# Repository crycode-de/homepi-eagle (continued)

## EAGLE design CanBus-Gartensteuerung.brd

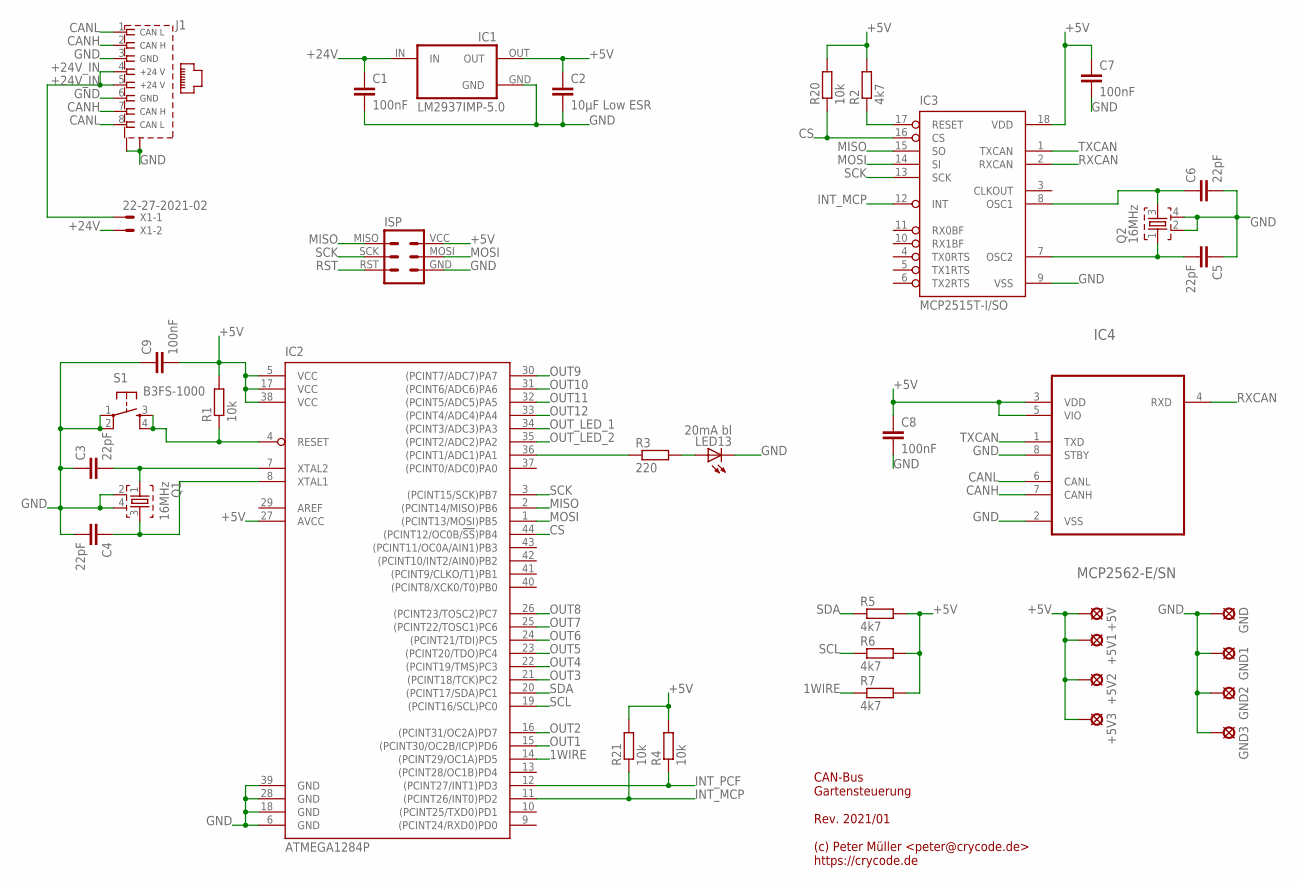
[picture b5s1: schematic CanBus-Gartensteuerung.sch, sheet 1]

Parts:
+5V, +5V1, +5V2, +5V3: LSP13
C1, C7, C8, C9: 100nF; C0805
C2: 10µF Low ESR; C0805
C3, C4, C5, C6: 22pF; C0805
GND, GND1, GND2, GND3: LSP13
IC1: LM2937IMP-5.0; SOT223
IC2: ATMEGA1284P; TQFP44
IC3: MCP2515T-I/SO; SO18L
IC4: MCP2562-E/SN; SO08
ISP: ISPVIAS-ONLY-1.27MM; ISP-VIAS-ONLY-1.27MM
J1: RJ45-CAN; MEBP_8-8G
LED13: 20mA bl; CHIPLED_0805
Q1, Q2: 16MHz; MJ-5X3.2
R1, R4, R20, R21: 10k; R0805
R2, R5, R6, R7: 4k7; R0805
R3: 220; R0805
S1: B3FS-1000
X1: 22-27-2021-02; 6410-02

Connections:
1WIRE: IC2.14 ((PCINT29/OC1A)PD5), R7.1; also elsewhere on the board
+5V: +5V.MP, +5V1.MP, +5V2.MP, +5V3.MP, C2.1, C7.1, C8.1, C9.2, IC1.OUT, IC2.5 (VCC), IC2.17 (VCC), IC2.27 (AVCC), IC2.38 (VCC), IC3.18 (VDD), IC4.3 (VDD), IC4.5 (VIO), ISP.VCC, R1.2, R2.2, R4.2, R5.2, R6.2, R7.2, R20.2, R21.2; also elsewhere on the board
+24V: C1.1, IC1.IN, X1.2; also elsewhere on the board
+24V_IN: J1.4, J1.5, X1.1
CANH: IC4.7 (CANH), J1.2, J1.7
CANL: IC4.6 (CANL), J1.1, J1.8
CS: IC2.44 ((PCINT12/OC0B/!SS!)PB4), IC3.16 (CS), R20.1
GND: C1.2, C2.2, C3.1, C4.2, C5.1, C6.2, C7.2, C8.2, C9.1, GND.MP, GND1.MP, GND2.MP, GND3.MP, IC1.GND, IC1.GND@ (GND), IC2.6 (GND), IC2.18 (GND), IC2.28 (GND), IC2.39 (GND), IC3.9 (VSS), IC4.2 (VSS), IC4.8 (STBY), ISP.GND, J1.3, J1.6, J1.G1 (S1), J1.G2 (S2), LED13.C, Q1.2, Q1.4, Q2.2, Q2.4, S1.1, S1.2 (P1); also elsewhere on the board
INT_MCP: IC2.11 ((PCINT26/INT0)PD2), IC3.12 (INT), R21.1
INT_PCF: IC2.12 ((PCINT27/INT1)PD3), R4.1; also elsewhere on the board
MISO: IC2.2 ((PCINT14/MISO)PB6), IC3.15 (SO), ISP.MISO
MOSI: IC2.1 ((PCINT13/MOSI)PB5), IC3.14 (SI), ISP.MOSI
unnamed: IC3.17 (RESET), R2.1
unnamed: IC2.36 ((PCINT1/ADC1)PA1), R3.1
unnamed: LED13.A, R3.2
OUT1: IC2.15 ((PCINT30/OC2B/ICP)PD6); also elsewhere on the board
OUT2: IC2.16 ((PCINT31/OC2A)PD7); also elsewhere on the board
OUT3: IC2.21 ((PCINT18/TCK)PC2); also elsewhere on the board
OUT4: IC2.22 ((PCINT19/TMS)PC3); also elsewhere on the board
OUT5: IC2.23 ((PCINT20/TDO)PC4); also elsewhere on the board
OUT6: IC2.24 ((PCINT21/TDI)PC5); also elsewhere on the board
OUT7: IC2.25 ((PCINT22/TOSC1)PC6); also elsewhere on the board
OUT8: IC2.26 ((PCINT23/TOSC2)PC7); also elsewhere on the board
OUT9: IC2.30 ((PCINT7/ADC7)PA7); also elsewhere on the board
OUT10: IC2.31 ((PCINT6/ADC6)PA6); also elsewhere on the board
OUT11: IC2.32 ((PCINT5/ADC5)PA5); also elsewhere on the board
OUT12: IC2.33 ((PCINT4/ADC4)PA4); also elsewhere on the board
OUT_LED_1: IC2.34 ((PCINT3/ADC3)PA3); also elsewhere on the board
OUT_LED_2: IC2.35 ((PCINT2/ADC2)PA2); also elsewhere on the board
RST: IC2.4 (RESET), ISP.RST, R1.1, S1.3 (S), S1.4 (S1)
RXCAN: IC3.2 (RXCAN), IC4.4 (RXD)
SCK: IC2.3 ((PCINT15/SCK)PB7), IC3.13 (SCK), ISP.SCK
SCL: IC2.19 ((PCINT16/SCL)PC0), R6.1; also elsewhere on the board
SDA: IC2.20 ((PCINT17/SDA)PC1), R5.1; also elsewhere on the board
TXCAN: IC3.1 (TXCAN), IC4.1 (TXD)
XTAL1: C3.2, IC2.7 (XTAL2), Q1.1
XTAL2: C4.1, IC2.8 (XTAL1), Q1.3
XTAL3: C5.2, IC3.7 (OSC2), Q2.1
XTAL4: C6.1, IC3.8 (OSC1), Q2.3

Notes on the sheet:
CAN-Bus Gartensteuerung Rev. 2021/01 (c) Peter Müller <peter@crycode.de> https://crycode.de

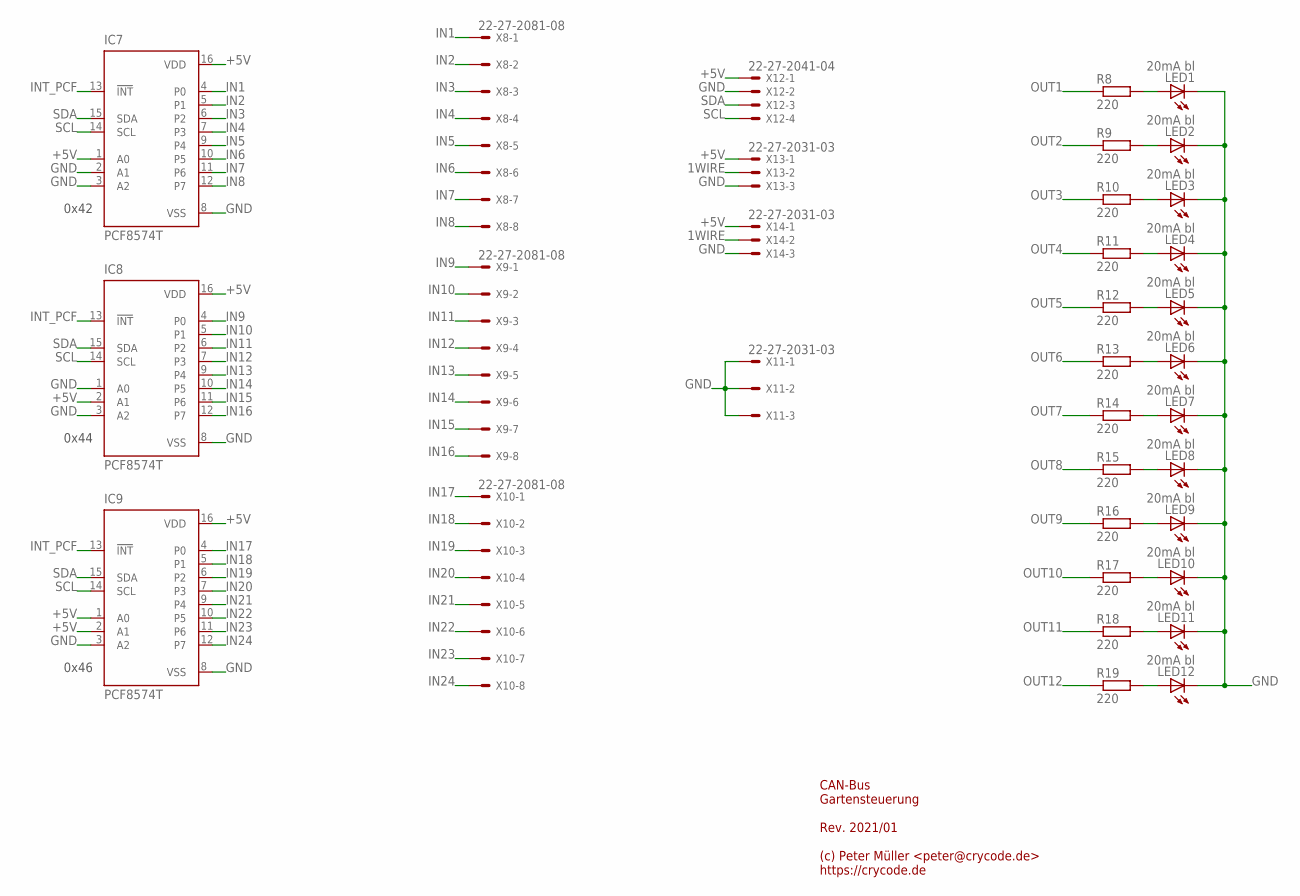
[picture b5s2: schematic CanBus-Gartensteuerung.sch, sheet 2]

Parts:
IC7, IC8, IC9: PCF8574T; SO16W
LED1, LED2, LED3, LED4, LED5, LED6, LED7, LED8, LED9, LED10, LED11, LED12: 20mA bl; CHIPLED_0805
R8, R9, R10, R11, R12, R13, R14, R15, R16, R17, R18, R19: 220; R0805
X8, X9, X10: 22-27-2081-08; 6410-08
X11, X13, X14: 22-27-2031-03; 6410-03
X12: 22-27-2041-04; 6410-04

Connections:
1WIRE: X13.2, X14.2; also elsewhere on the board
+5V: IC7.1 (A0), IC7.16 (VDD), IC8.2 (A1), IC8.16 (VDD), IC9.1 (A0), IC9.2 (A1), IC9.16 (VDD), X12.1, X13.1, X14.1; also elsewhere on the board
GND: IC7.2 (A1), IC7.3 (A2), IC7.8 (VSS), IC8.1 (A0), IC8.3 (A2), IC8.8 (VSS), IC9.3 (A2), IC9.8 (VSS), LED1.C, LED2.C, LED3.C, LED4.C, LED5.C, LED6.C, LED7.C, LED8.C, LED9.C, LED10.C, LED11.C, LED12.C, X11.1, X11.2, X11.3, X12.2, X13.3, X14.3; also elsewhere on the board
IN1: IC7.4 (P0), X8.1
IN2: IC7.5 (P1), X8.2
IN3: IC7.6 (P2), X8.3
IN4: IC7.7 (P3), X8.4
IN5: IC7.9 (P4), X8.5
IN6: IC7.10 (P5), X8.6
IN7: IC7.11 (P6), X8.7
IN8: IC7.12 (P7), X8.8
IN9: IC8.4 (P0), X9.1
IN10: IC8.5 (P1), X9.2
IN11: IC8.6 (P2), X9.3
IN12: IC8.7 (P3), X9.4
IN13: IC8.9 (P4), X9.5
IN14: IC8.10 (P5), X9.6
IN15: IC8.11 (P6), X9.7
IN16: IC8.12 (P7), X9.8
IN17: IC9.4 (P0), X10.1
IN18: IC9.5 (P1), X10.2
IN19: IC9.6 (P2), X10.3
IN20: IC9.7 (P3), X10.4
IN21: IC9.9 (P4), X10.5
IN22: IC9.10 (P5), X10.6
IN23: IC9.11 (P6), X10.7
IN24: IC9.12 (P7), X10.8
INT_PCF: IC7.13 (!INT), IC8.13 (!INT), IC9.13 (!INT); also elsewhere on the board
unnamed: LED1.A, R8.2
unnamed: LED2.A, R9.2
unnamed: LED3.A, R10.2
unnamed: LED4.A, R11.2
unnamed: LED5.A, R12.2
unnamed: LED6.A, R13.2
unnamed: LED7.A, R14.2
unnamed: LED8.A, R15.2
unnamed: LED9.A, R16.2
unnamed: LED10.A, R17.2
unnamed: LED12.A, R19.2
unnamed: LED11.A, R18.2
OUT1: R8.1; also elsewhere on the board
OUT2: R9.1; also elsewhere on the board
OUT3: R10.1; also elsewhere on the board
OUT4: R11.1; also elsewhere on the board
OUT5: R12.1; also elsewhere on the board
OUT6: R13.1; also elsewhere on the board
OUT7: R14.1; also elsewhere on the board
OUT8: R15.1; also elsewhere on the board
OUT9: R16.1; also elsewhere on the board
OUT10: R17.1; also elsewhere on the board
OUT11: R18.1; also elsewhere on the board
OUT12: R19.1; also elsewhere on the board
SCL: IC7.14 (SCL), IC8.14 (SCL), IC9.14 (SCL), X12.4; also elsewhere on the board
SDA: IC7.15 (SDA), IC8.15 (SDA), IC9.15 (SDA), X12.3; also elsewhere on the board

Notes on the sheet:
0x42
0x44
0x46
CAN-Bus Gartensteuerung Rev. 2021/01 (c) Peter Müller <peter@crycode.de> https://crycode.de

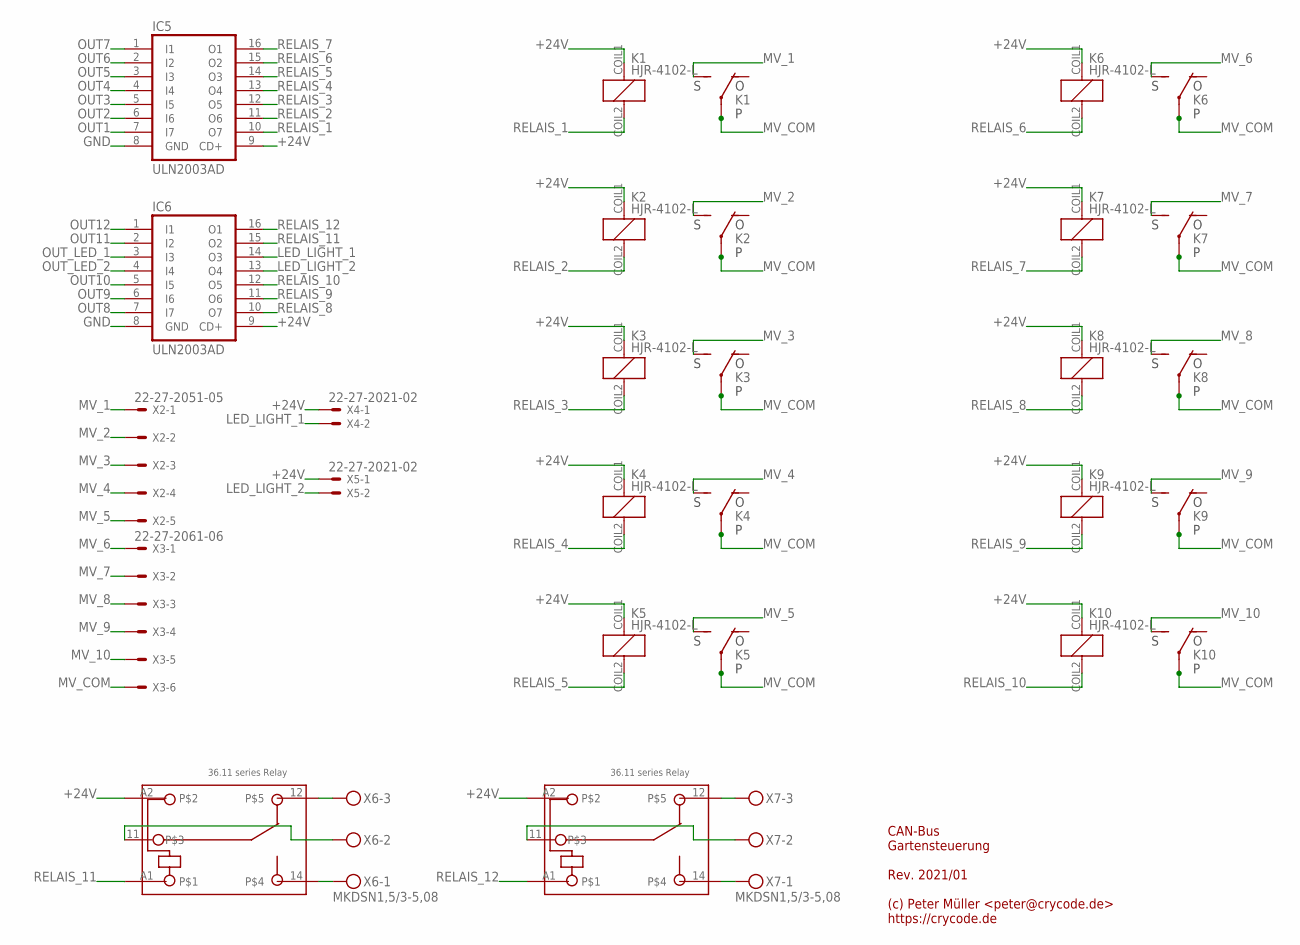
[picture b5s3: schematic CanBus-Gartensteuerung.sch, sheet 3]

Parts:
IC5, IC6: ULN2003AD; SO16
K1, K2, K3, K4, K5, K6, K7, K8, K9, K10: HJR-4102-L; HJR4102
K11, K12: 36.11
X2: 22-27-2051-05; 6410-05
X3: 22-27-2061-06; 6410-06
X4, X5: 22-27-2021-02; 6410-02
X6, X7: MKDSN1,5/3-5,08

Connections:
+24V: IC5.9 (CD+), IC6.9 (CD+), K1.COIL1 (1), K2.COIL1 (1), K3.COIL1 (1), K4.COIL1 (1), K5.COIL1 (1), K6.COIL1 (1), K7.COIL1 (1), K8.COIL1 (1), K9.COIL1 (1), K10.COIL1 (1), K11.A2, K12.A2, X4.1, X5.1; also elsewhere on the board
GND: IC5.8 (GND), IC6.8 (GND); also elsewhere on the board
LED_LIGHT_1: IC6.14 (O3), X4.2
LED_LIGHT_2: IC6.13 (O4), X5.2
MV_1: K1.CON1DEFAULT (S), X2.1
MV_2: K2.CON1DEFAULT (S), X2.2
MV_3: K3.CON1DEFAULT (S), X2.3
MV_4: K4.CON1DEFAULT (S), X2.4
MV_5: K5.CON1DEFAULT (S), X2.5
MV_6: K6.CON1DEFAULT (S), X3.1
MV_7: K7.CON1DEFAULT (S), X3.2
MV_8: K8.CON1DEFAULT (S), X3.3
MV_9: K9.CON1DEFAULT (S), X3.4
MV_10: K10.CON1DEFAULT (S), X3.5
MV_COM: K1.CENTER1, K1.CENTER2 (P2), K2.CENTER1, K2.CENTER2 (P2), K3.CENTER1, K3.CENTER2 (P2), K4.CENTER1, K4.CENTER2 (P2), K5.CENTER1, K5.CENTER2 (P2), K6.CENTER1, K6.CENTER2 (P2), K7.CENTER1, K7.CENTER2 (P2), K8.CENTER1, K8.CENTER2 (P2), K9.CENTER1, K9.CENTER2 (P2), K10.CENTER1, K10.CENTER2 (P2), X3.6
unnamed: K11.12, X6.3
unnamed: K11.14, X6.1
unnamed: K12.12, X7.3
unnamed: K12.14, X7.1
unnamed: K11.11, X6.2
unnamed: K12.11, X7.2
OUT1: IC5.7 (I7); also elsewhere on the board
OUT2: IC5.6 (I6); also elsewhere on the board
OUT3: IC5.5 (I5); also elsewhere on the board
OUT4: IC5.4 (I4); also elsewhere on the board
OUT5: IC5.3 (I3); also elsewhere on the board
OUT6: IC5.2 (I2); also elsewhere on the board
OUT7: IC5.1 (I1); also elsewhere on the board
OUT8: IC6.7 (I7); also elsewhere on the board
OUT9: IC6.6 (I6); also elsewhere on the board
OUT10: IC6.5 (I5); also elsewhere on the board
OUT11: IC6.2 (I2); also elsewhere on the board
OUT12: IC6.1 (I1); also elsewhere on the board
OUT_LED_1: IC6.3 (I3); also elsewhere on the board
OUT_LED_2: IC6.4 (I4); also elsewhere on the board
RELAIS_1: IC5.10 (O7), K1.COIL2 (2)
RELAIS_2: IC5.11 (O6), K2.COIL2 (2)
RELAIS_3: IC5.12 (O5), K3.COIL2 (2)
RELAIS_4: IC5.13 (O4), K4.COIL2 (2)
RELAIS_5: IC5.14 (O3), K5.COIL2 (2)
RELAIS_6: IC5.15 (O2), K6.COIL2 (2)
RELAIS_7: IC5.16 (O1), K7.COIL2 (2)
RELAIS_8: IC6.10 (O7), K8.COIL2 (2)
RELAIS_9: IC6.11 (O6), K9.COIL2 (2)
RELAIS_10: IC6.12 (O5), K10.COIL2 (2)
RELAIS_11: IC6.15 (O2), K11.A1
RELAIS_12: IC6.16 (O1), K12.A1

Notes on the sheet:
CAN-Bus Gartensteuerung Rev. 2021/01 (c) Peter Müller <peter@crycode.de> https://crycode.de

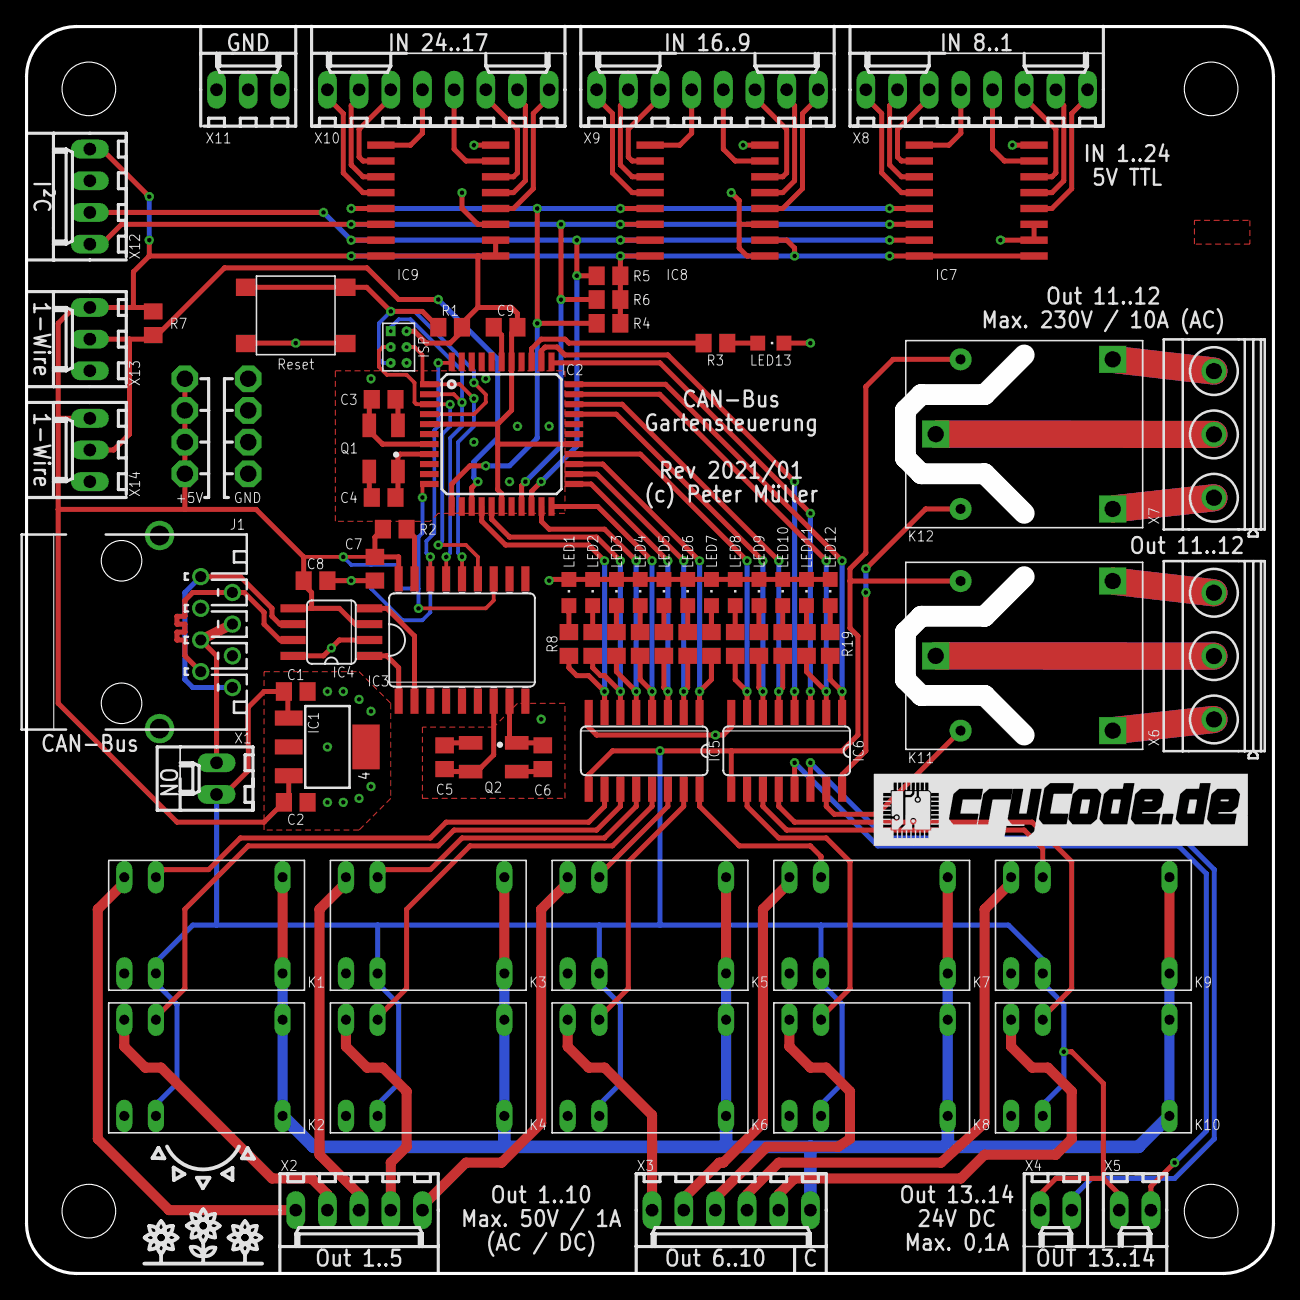
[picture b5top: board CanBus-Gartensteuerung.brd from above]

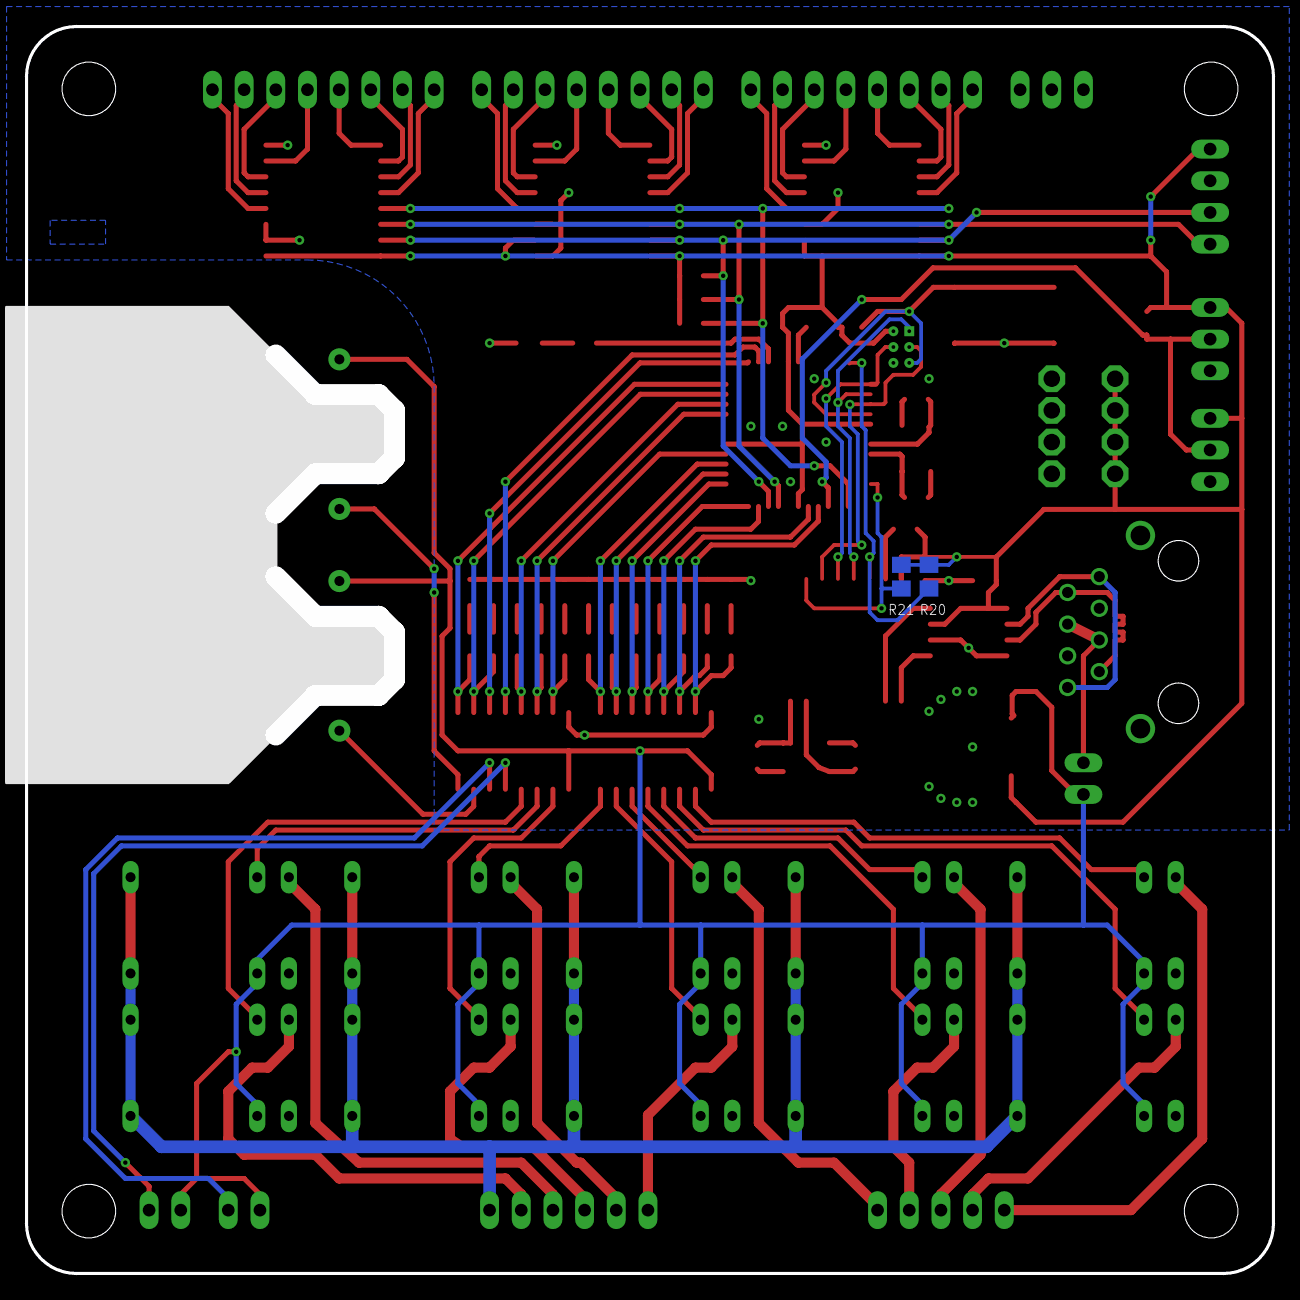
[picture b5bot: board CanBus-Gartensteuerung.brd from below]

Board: 2 copper layers, 100.0 x 100.0 mm, 92 parts (2 on the bottom side), 106 nets.

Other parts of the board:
U$2: 30MM

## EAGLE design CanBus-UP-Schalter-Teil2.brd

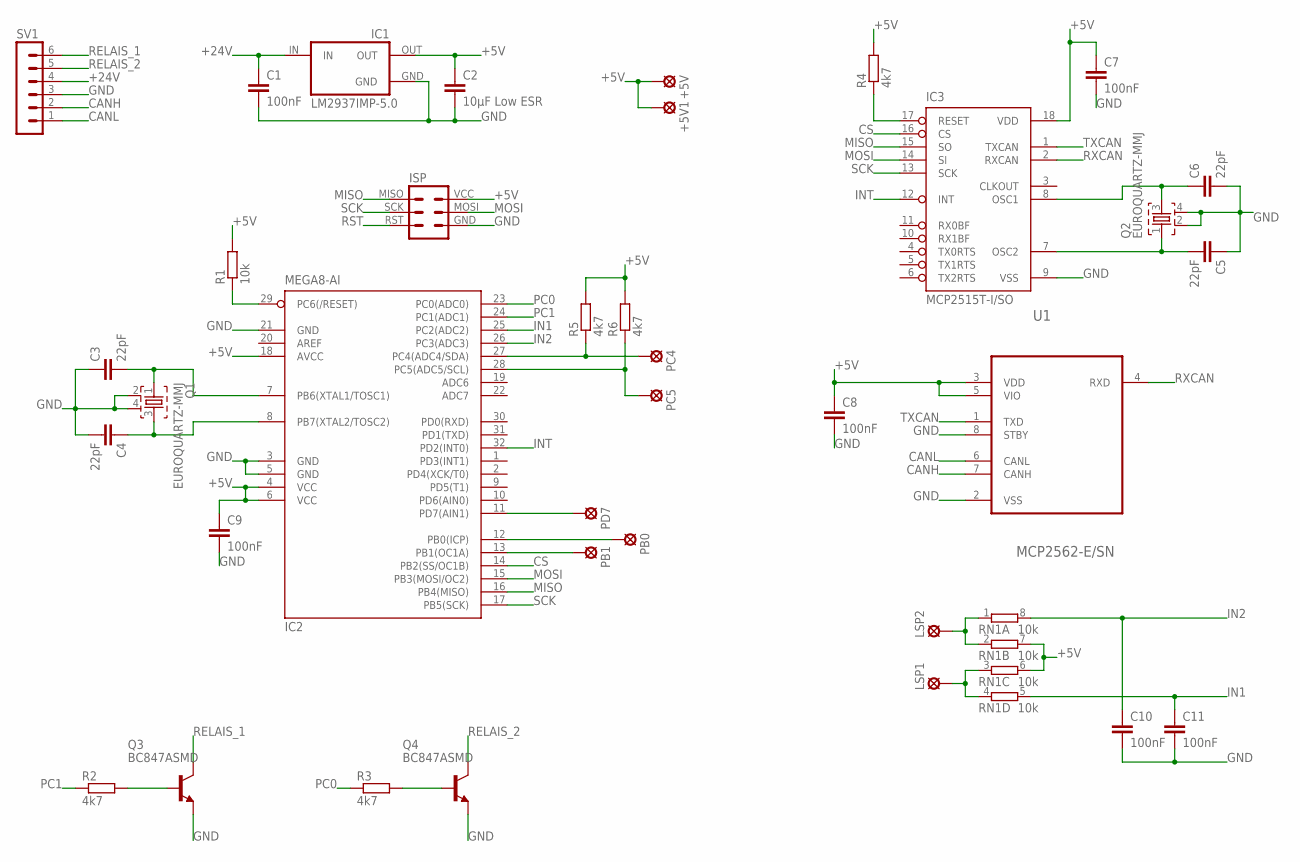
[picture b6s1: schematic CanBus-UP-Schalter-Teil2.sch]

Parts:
+5V, +5V1: LSP13
C1, C7, C8, C9, C10, C11: 100nF; C0805
C2: 10µF Low ESR; C0805
C3, C4, C5, C6: 22pF; C0805
IC1: LM2937IMP-5.0; SOT223
IC2: MEGA8-AI; TQFP32-08
IC3: MCP2515T-I/SO; SO18L
ISP: ISPVIAS-ONLY-1.27MM; ISP-VIAS-ONLY-1.27MM
LSP1, LSP2: LSP13
PB0, PB1: LSP13
PC4, PC5: LSP13
PD7: LSP13
Q1, Q2: EUROQUARTZ-MMJ; MJ-5X3.2
Q3, Q4: BC847ASMD; SOT23
R1: 10k; R0805
R2, R3, R4, R5, R6: 4k7; R0805
RN1: 10k; 0603-ARC
SV1: MA06-1
U1: MCP2562-E/SN; SO08

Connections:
+5V: +5V.MP, +5V1.MP, C2.1, C7.1, C8.1, C9.1, IC1.OUT, IC2.4 (VCC), IC2.6 (VCC), IC2.18 (AVCC), IC3.18 (VDD), ISP.VCC, R1.2, R4.2, R5.2, R6.2, RN1.6 (2), RN1.7 (2), U1.3 (VDD), U1.5 (VIO)
+24V: C1.1, IC1.IN, SV1.4
CANH: SV1.2, U1.7 (CANH)
CANL: SV1.1, U1.6 (CANL)
CS: IC2.14 (PB2(SS/OC1B)), IC3.16 (CS)
GND: C1.2, C2.2, C3.1, C4.2, C5.1, C6.2, C7.2, C8.2, C9.2, C10.2, C11.2, IC1.GND, IC1.GND@ (GND), IC2.3 (GND), IC2.5 (GND), IC2.21 (GND), IC3.9 (VSS), ISP.GND, Q1.2, Q1.4, Q2.2, Q2.4, Q3.2 (E), Q4.2 (E), SV1.3, U1.2 (VSS), U1.8 (STBY)
IN1: C11.1, IC2.25 (PC2(ADC2)), RN1.5 (2)
IN2: C10.1, IC2.26 (PC3(ADC3)), RN1.8 (2)
INT: IC2.32 (PD2(INT0)), IC3.12 (INT)
MISO: IC2.16 (PB4(MISO)), IC3.15 (SO), ISP.MISO
MOSI: IC2.15 (PB3(MOSI/OC2)), IC3.14 (SI), ISP.MOSI
unnamed: IC3.17 (RESET), R4.1
unnamed: Q3.1 (B), R2.2
unnamed: Q4.1 (B), R3.2
unnamed: LSP1.MP, RN1.3 (1), RN1.4 (1)
unnamed: LSP2.MP, RN1.1, RN1.2 (1)
unnamed: IC2.13 (PB1(OC1A)), PB1.MP
unnamed: IC2.12 (PB0(ICP)), PB0.MP
unnamed: IC2.11 (PD7(AIN1)), PD7.MP
unnamed: IC2.28 (PC5(ADC5/SCL)), PC5.MP, R6.1
unnamed: IC2.27 (PC4(ADC4/SDA)), PC4.MP, R5.1
PC0: IC2.23 (PC0(ADC0)), R3.1
PC1: IC2.24 (PC1(ADC1)), R2.1
RELAIS_1: Q3.3 (C), SV1.6
RELAIS_2: Q4.3 (C), SV1.5
RST: IC2.29 (PC6(/RESET)), ISP.RST, R1.1
RXCAN: IC3.2 (RXCAN), U1.4 (RXD)
SCK: IC2.17 (PB5(SCK)), IC3.13 (SCK), ISP.SCK
TXCAN: IC3.1 (TXCAN), U1.1 (TXD)
XTAL1: C3.2, IC2.7 (PB6(XTAL1/TOSC1)), Q1.1
XTAL2: C4.1, IC2.8 (PB7(XTAL2/TOSC2)), Q1.3
XTAL3: C5.2, IC3.7 (OSC2), Q2.1
XTAL4: C6.1, IC3.8 (OSC1), Q2.3

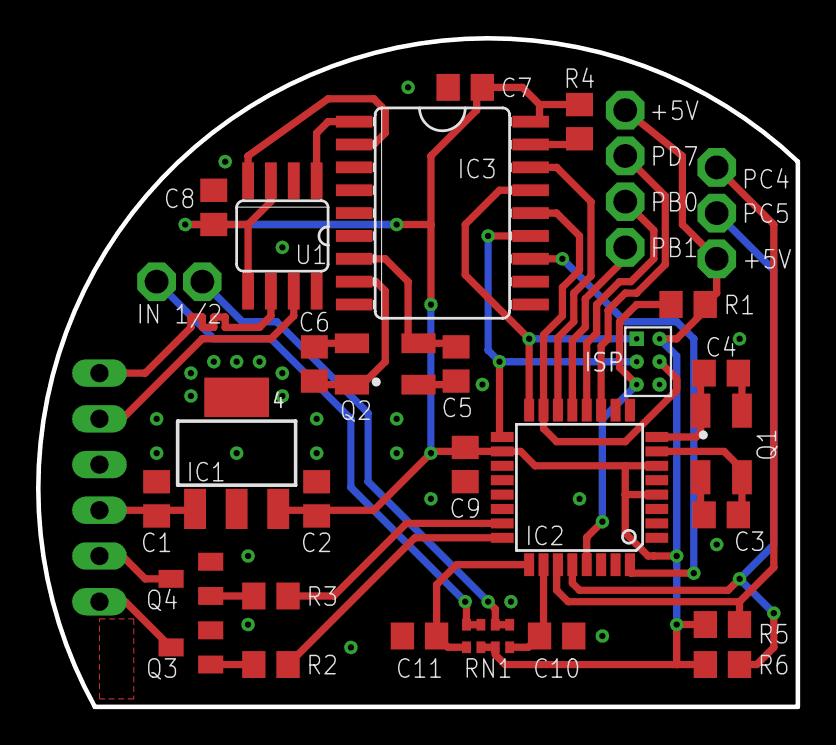
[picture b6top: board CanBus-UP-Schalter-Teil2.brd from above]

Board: 2 copper layers, 42.2 x 37.1 mm, 37 parts (1 on the bottom side), 33 nets.

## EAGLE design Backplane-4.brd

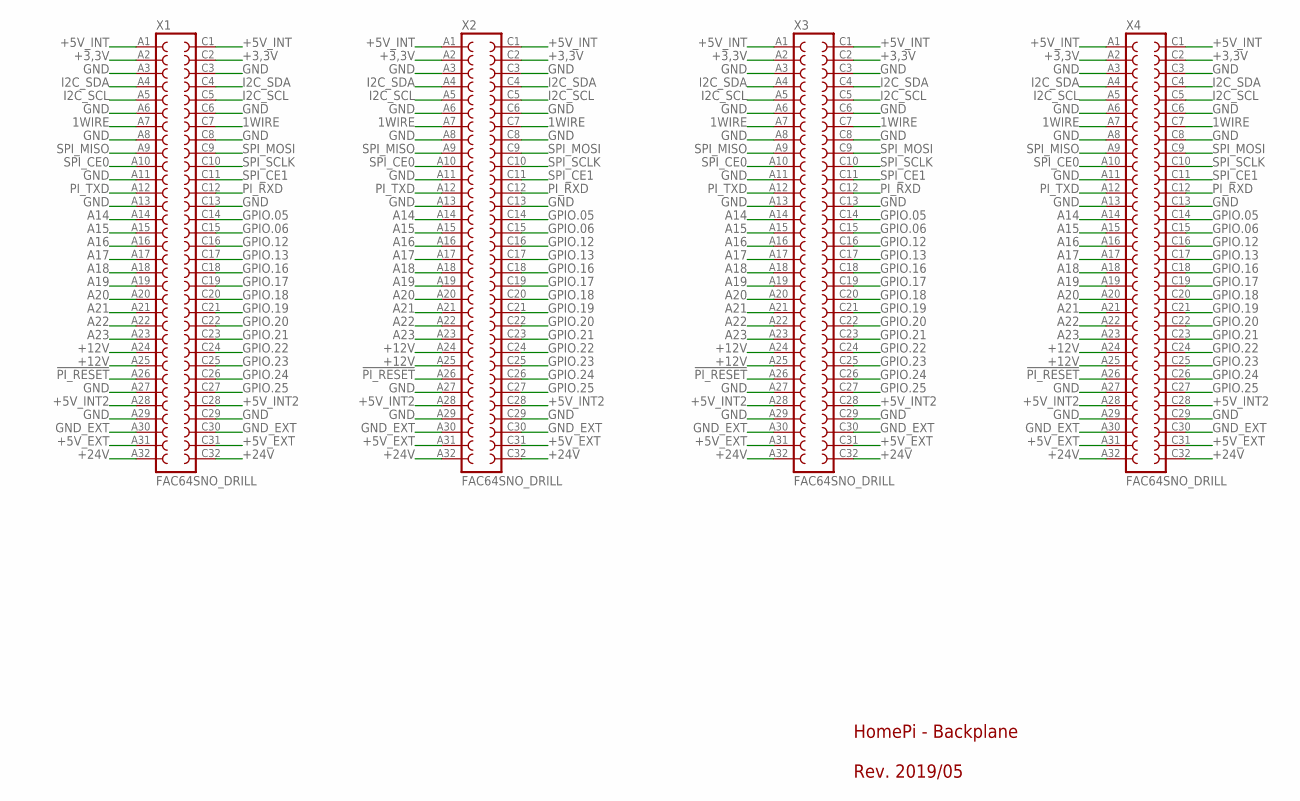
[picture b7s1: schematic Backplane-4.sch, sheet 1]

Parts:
X1, X2, X3, X4: FAC64SNO_DRILL; FAC64S_NO_DRILL

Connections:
1WIRE: X1.A7, X1.C7, X2.A7, X2.C7, X3.A7, X3.C7, X4.A7, X4.C7; also elsewhere on the board
!PI_RESET: X1.A26, X2.A26, X3.A26, X4.A26; also elsewhere on the board
+3,3V: X1.A2, X1.C2, X2.A2, X2.C2, X3.A2, X3.C2, X4.A2, X4.C2; also elsewhere on the board
+5V_EXT: X1.A31, X1.C31, X2.A31, X2.C31, X3.A31, X3.C31, X4.A31, X4.C31; also elsewhere on the board
+5V_INT: X1.A1, X1.C1, X2.A1, X2.C1, X3.A1, X3.C1, X4.A1, X4.C1; also elsewhere on the board
+5V_INT2: X1.A28, X1.C28, X2.A28, X2.C28, X3.A28, X3.C28, X4.A28, X4.C28; also elsewhere on the board
+12V: X1.A24, X1.A25, X2.A24, X2.A25, X3.A24, X3.A25, X4.A24, X4.A25; also elsewhere on the board
+24V: X1.A32, X1.C32, X2.A32, X2.C32, X3.A32, X3.C32, X4.A32, X4.C32; also elsewhere on the board
A14: X1.A14, X2.A14, X3.A14, X4.A14; also elsewhere on the board
A15: X1.A15, X2.A15, X3.A15, X4.A15; also elsewhere on the board
A16: X1.A16, X2.A16, X3.A16, X4.A16; also elsewhere on the board
A17: X1.A17, X2.A17, X3.A17, X4.A17; also elsewhere on the board
A18: X1.A18, X2.A18, X3.A18, X4.A18; also elsewhere on the board
A19: X1.A19, X2.A19, X3.A19, X4.A19; also elsewhere on the board
A20: X1.A20, X2.A20, X3.A20, X4.A20; also elsewhere on the board
A21: X1.A21, X2.A21, X3.A21, X4.A21; also elsewhere on the board
A22: X1.A22, X2.A22, X3.A22, X4.A22; also elsewhere on the board
A23: X1.A23, X2.A23, X3.A23, X4.A23; also elsewhere on the board
GND: X1.A3, X1.A6, X1.A8, X1.A11, X1.A13, X1.A27, X1.A29, X1.C3, X1.C6, X1.C8, X1.C13, X1.C29, X2.A3, X2.A6, X2.A8, X2.A11, X2.A13, X2.A27, X2.A29, X2.C3, X2.C6, X2.C8, X2.C13, X2.C29, X3.A3, X3.A6, X3.A8, X3.A11, X3.A13, X3.A27, X3.A29, X3.C3, X3.C6, X3.C8, X3.C13, X3.C29, X4.A3, X4.A6, X4.A8, X4.A11, X4.A13, X4.A27, X4.A29, X4.C3, X4.C6, X4.C8, X4.C13, X4.C29; also elsewhere on the board
GND_EXT: X1.A30, X1.C30, X2.A30, X2.C30, X3.A30, X3.C30, X4.A30, X4.C30; also elsewhere on the board
GPIO.05: X1.C14, X2.C14, X3.C14, X4.C14; also elsewhere on the board
GPIO.06: X1.C15, X2.C15, X3.C15, X4.C15; also elsewhere on the board
GPIO.12: X1.C16, X2.C16, X3.C16, X4.C16; also elsewhere on the board
GPIO.13: X1.C17, X2.C17, X3.C17, X4.C17; also elsewhere on the board
GPIO.16: X1.C18, X2.C18, X3.C18, X4.C18; also elsewhere on the board
GPIO.17: X1.C19, X2.C19, X3.C19, X4.C19; also elsewhere on the board
GPIO.18: X1.C20, X2.C20, X3.C20, X4.C20; also elsewhere on the board
GPIO.19: X1.C21, X2.C21, X3.C21, X4.C21; also elsewhere on the board
GPIO.20: X1.C22, X2.C22, X3.C22, X4.C22; also elsewhere on the board
GPIO.21: X1.C23, X2.C23, X3.C23, X4.C23; also elsewhere on the board
GPIO.22: X1.C24, X2.C24, X3.C24, X4.C24; also elsewhere on the board
GPIO.23: X1.C25, X2.C25, X3.C25, X4.C25; also elsewhere on the board
GPIO.24: X1.C26, X2.C26, X3.C26, X4.C26; also elsewhere on the board
GPIO.25: X1.C27, X2.C27, X3.C27, X4.C27; also elsewhere on the board
I2C_SCL: X1.A5, X1.C5, X2.A5, X2.C5, X3.A5, X3.C5, X4.A5, X4.C5; also elsewhere on the board
I2C_SDA: X1.A4, X1.C4, X2.A4, X2.C4, X3.A4, X3.C4, X4.A4, X4.C4; also elsewhere on the board
PI_RXD: X1.C12, X2.C12, X3.C12, X4.C12; also elsewhere on the board
PI_TXD: X1.A12, X2.A12, X3.A12, X4.A12; also elsewhere on the board
SPI_CE0: X1.A10, X2.A10, X3.A10, X4.A10; also elsewhere on the board
SPI_CE1: X1.C11, X2.C11, X3.C11, X4.C11; also elsewhere on the board
SPI_MISO: X1.A9, X2.A9, X3.A9, X4.A9; also elsewhere on the board
SPI_MOSI: X1.C9, X2.C9, X3.C9, X4.C9; also elsewhere on the board
SPI_SCLK: X1.C10, X2.C10, X3.C10, X4.C10; also elsewhere on the board

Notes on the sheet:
HomePi - Backplane Rev. 2019/05

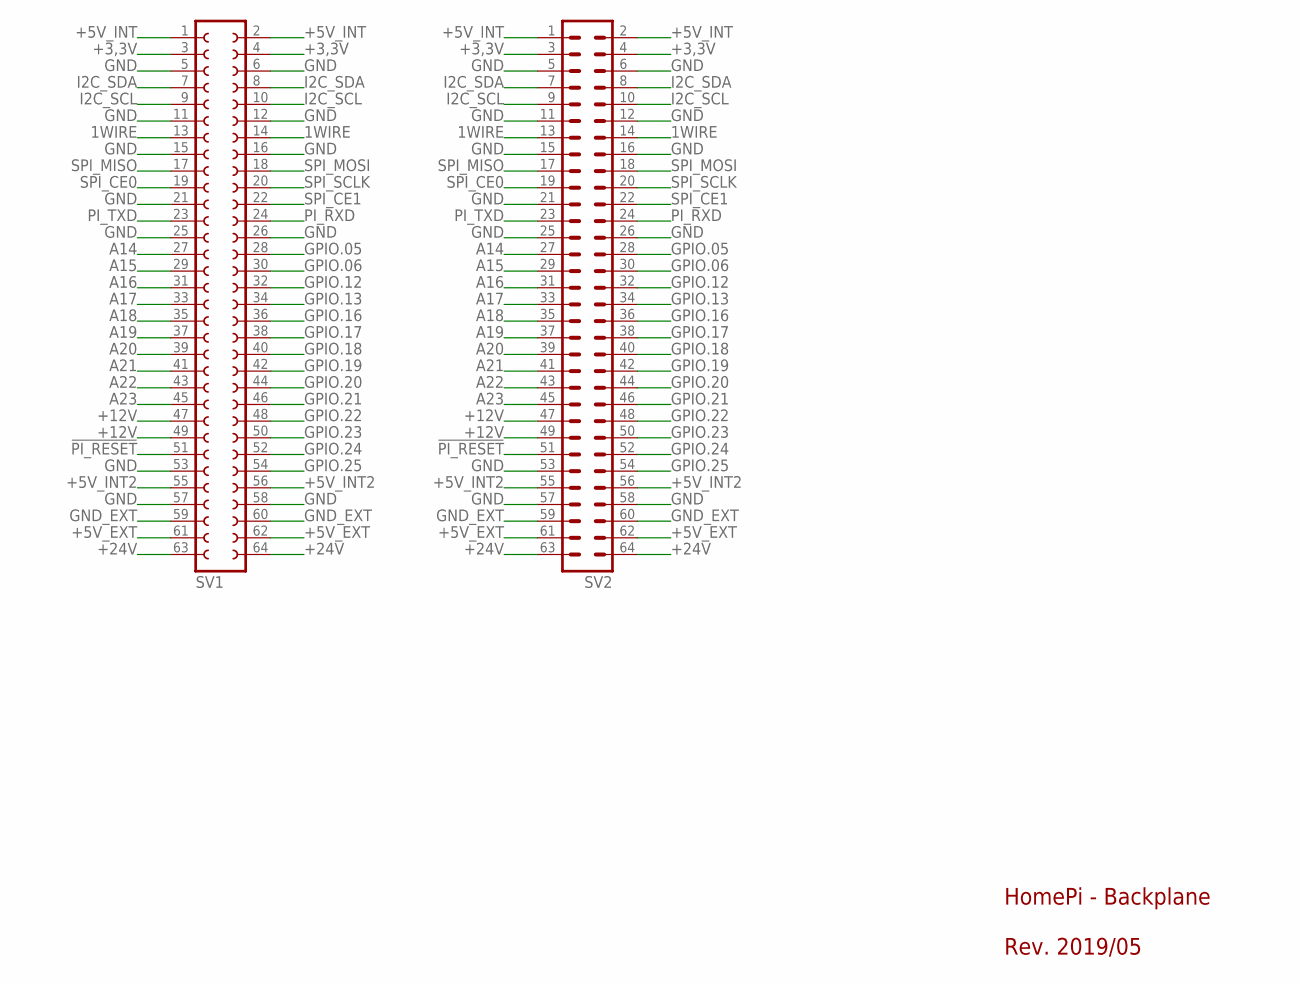
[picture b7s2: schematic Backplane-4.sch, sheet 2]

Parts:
SV1: FE32-2W
SV2: MA32-2W

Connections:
1WIRE: SV1.13, SV1.14, SV2.13, SV2.14; also elsewhere on the board
!PI_RESET: SV1.51, SV2.51; also elsewhere on the board
+3,3V: SV1.3, SV1.4, SV2.3, SV2.4; also elsewhere on the board
+5V_EXT: SV1.61, SV1.62, SV2.61, SV2.62; also elsewhere on the board
+5V_INT: SV1.1, SV1.2, SV2.1, SV2.2; also elsewhere on the board
+5V_INT2: SV1.55, SV1.56, SV2.55, SV2.56; also elsewhere on the board
+12V: SV1.47, SV1.49, SV2.47, SV2.49; also elsewhere on the board
+24V: SV1.63, SV1.64, SV2.63, SV2.64; also elsewhere on the board
A14: SV1.27, SV2.27; also elsewhere on the board
A15: SV1.29, SV2.29; also elsewhere on the board
A16: SV1.31, SV2.31; also elsewhere on the board
A17: SV1.33, SV2.33; also elsewhere on the board
A18: SV1.35, SV2.35; also elsewhere on the board
A19: SV1.37, SV2.37; also elsewhere on the board
A20: SV1.39, SV2.39; also elsewhere on the board
A21: SV1.41, SV2.41; also elsewhere on the board
A22: SV1.43, SV2.43; also elsewhere on the board
A23: SV1.45, SV2.45; also elsewhere on the board
GND: SV1.5, SV1.6, SV1.11, SV1.12, SV1.15, SV1.16, SV1.21, SV1.25, SV1.26, SV1.53, SV1.57, SV1.58, SV2.5, SV2.6, SV2.11, SV2.12, SV2.15, SV2.16, SV2.21, SV2.25, SV2.26, SV2.53, SV2.57, SV2.58; also elsewhere on the board
GND_EXT: SV1.59, SV1.60, SV2.59, SV2.60; also elsewhere on the board
GPIO.05: SV1.28, SV2.28; also elsewhere on the board
GPIO.06: SV1.30, SV2.30; also elsewhere on the board
GPIO.12: SV1.32, SV2.32; also elsewhere on the board
GPIO.13: SV1.34, SV2.34; also elsewhere on the board
GPIO.16: SV1.36, SV2.36; also elsewhere on the board
GPIO.17: SV1.38, SV2.38; also elsewhere on the board
GPIO.18: SV1.40, SV2.40; also elsewhere on the board
GPIO.19: SV1.42, SV2.42; also elsewhere on the board
GPIO.20: SV1.44, SV2.44; also elsewhere on the board
GPIO.21: SV1.46, SV2.46; also elsewhere on the board
GPIO.22: SV1.48, SV2.48; also elsewhere on the board
GPIO.23: SV1.50, SV2.50; also elsewhere on the board
GPIO.24: SV1.52, SV2.52; also elsewhere on the board
GPIO.25: SV1.54, SV2.54; also elsewhere on the board
I2C_SCL: SV1.9, SV1.10, SV2.9, SV2.10; also elsewhere on the board
I2C_SDA: SV1.7, SV1.8, SV2.7, SV2.8; also elsewhere on the board
PI_RXD: SV1.24, SV2.24; also elsewhere on the board
PI_TXD: SV1.23, SV2.23; also elsewhere on the board
SPI_CE0: SV1.19, SV2.19; also elsewhere on the board
SPI_CE1: SV1.22, SV2.22; also elsewhere on the board
SPI_MISO: SV1.17, SV2.17; also elsewhere on the board
SPI_MOSI: SV1.18, SV2.18; also elsewhere on the board
SPI_SCLK: SV1.20, SV2.20; also elsewhere on the board

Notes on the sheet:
HomePi - Backplane Rev. 2019/05

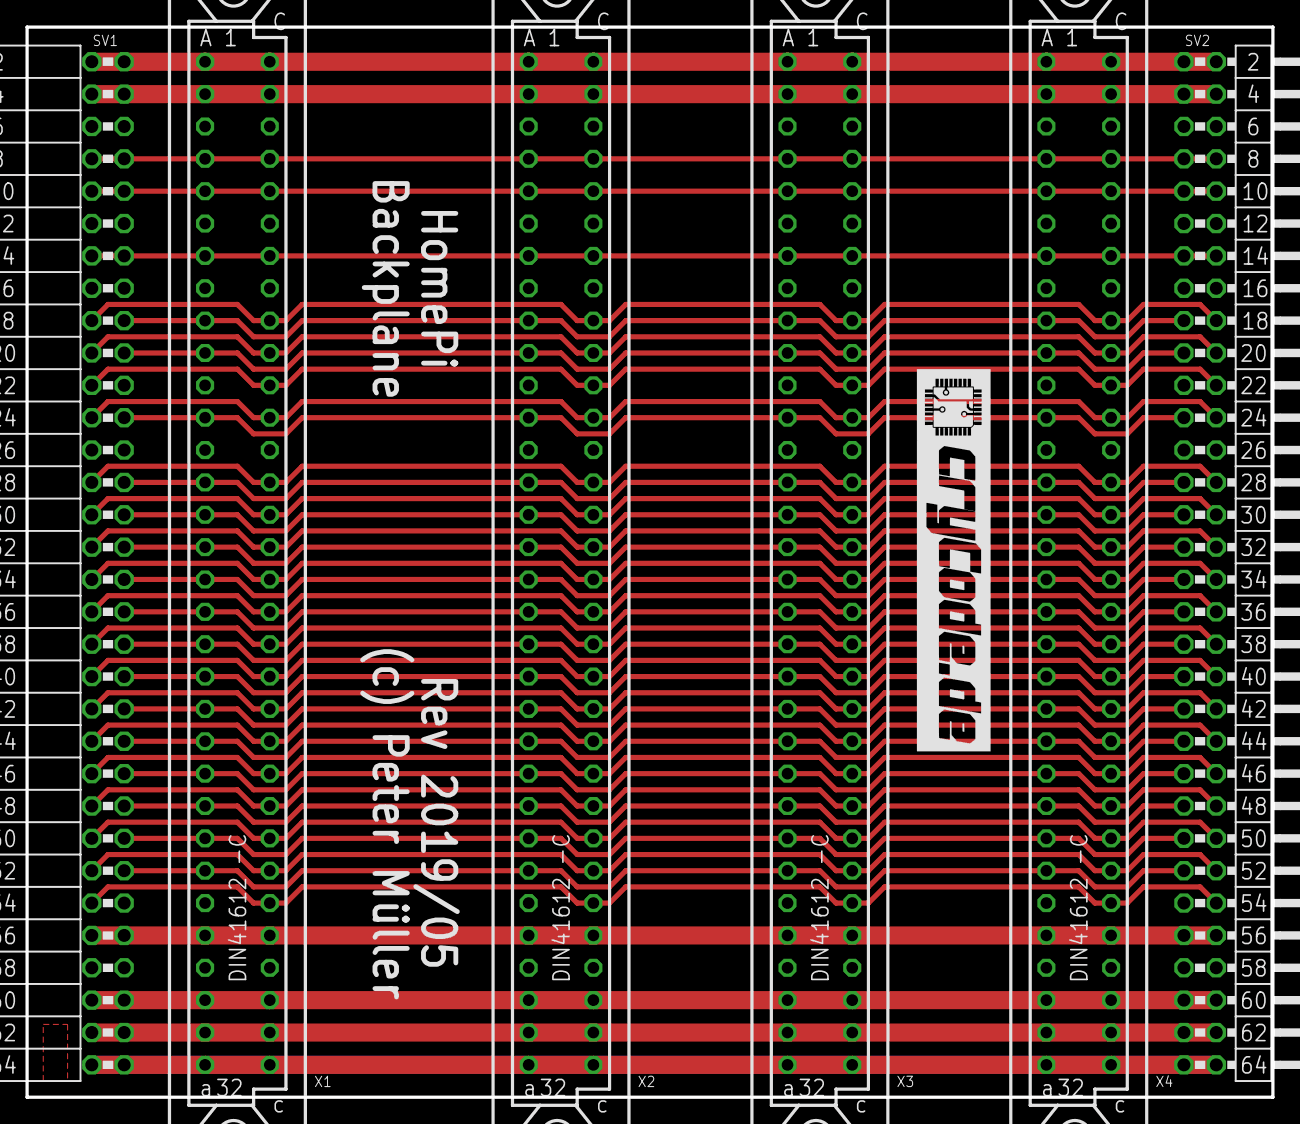
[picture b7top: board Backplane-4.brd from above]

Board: 2 copper layers, 97.8 x 84.0 mm, 8 parts (1 on the bottom side), 43 nets.

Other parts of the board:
U$1, U$2: 30MM
